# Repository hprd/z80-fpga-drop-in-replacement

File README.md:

# z80-fpga-drop-in-replacement
UT Austin Fall 2025-Spring 2026 Senior Design Project for developing a Zilog Z80 CPU drop-in replacement using an FPGA.

Relevant links and information from previous group's iteration:
- [Instruction Set](https://map.grauw.nl/resources/z80instr.php)
- [Z80 User Manual](https://www.zilog.com/docs/z80/um0080.pdf)
- [Master Reference Website](http://z80.info/)
- [Timing Quirks](https://floooh.github.io/2021/12/06/z80-instruction-timing.html#extra-clock-cycles)

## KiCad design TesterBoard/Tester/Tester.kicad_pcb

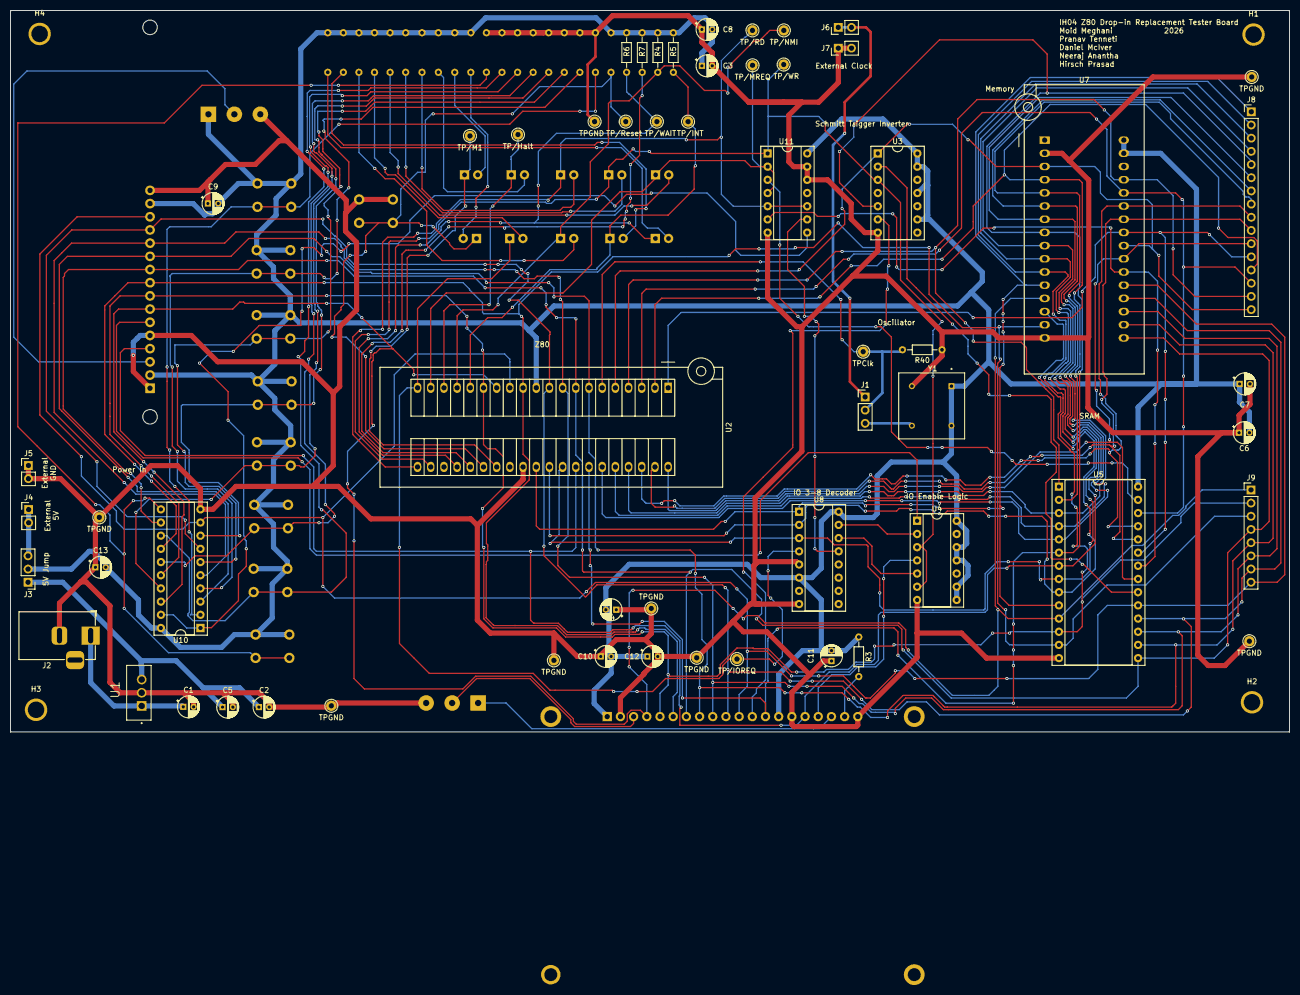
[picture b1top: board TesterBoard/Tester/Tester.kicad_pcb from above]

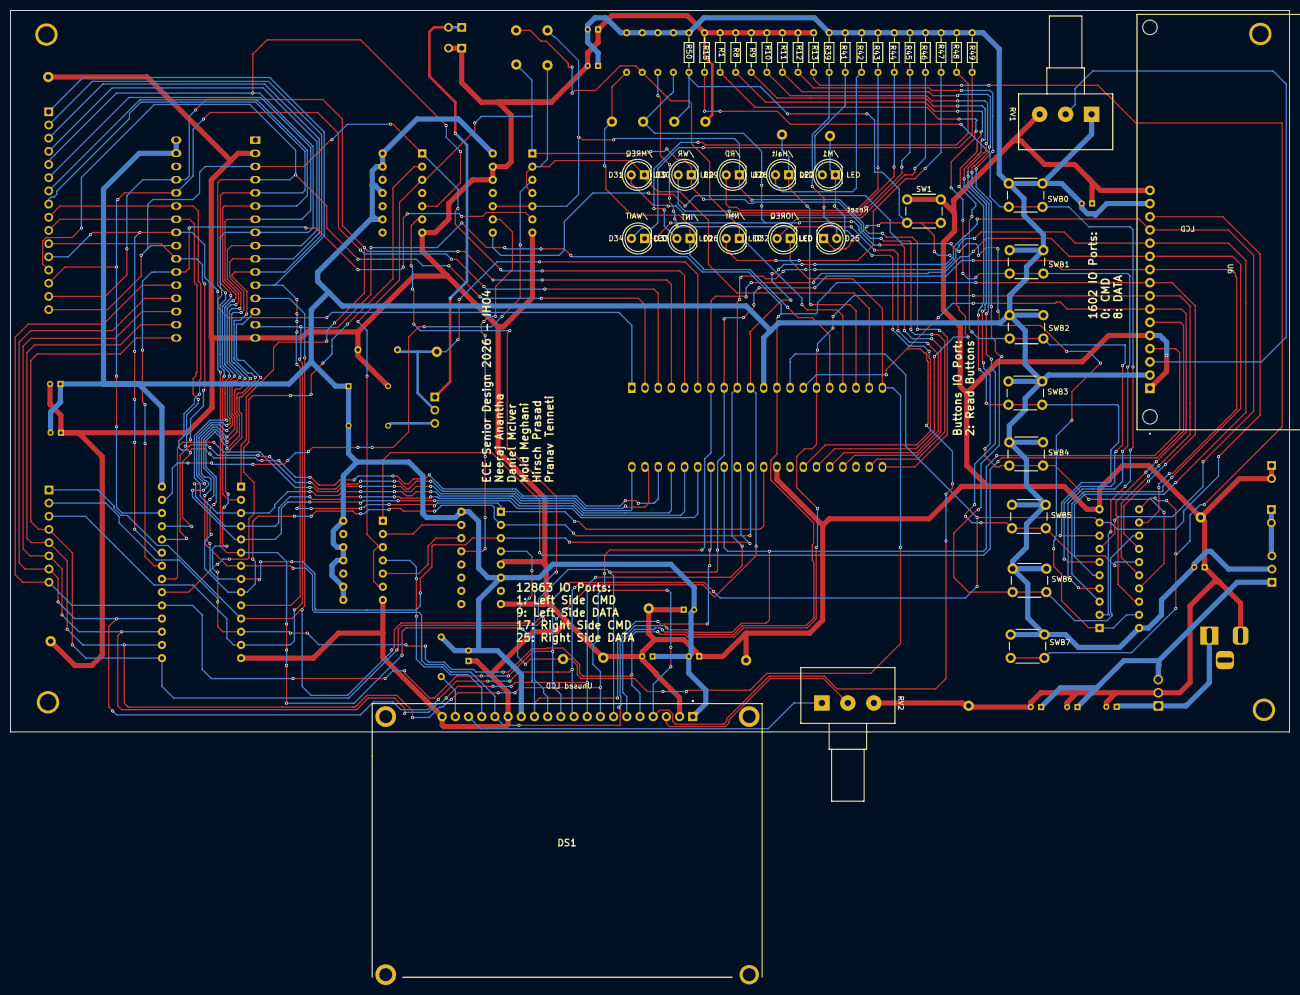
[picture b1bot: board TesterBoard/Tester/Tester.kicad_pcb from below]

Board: 2 copper layers, 246.3 x 138.9 mm, 103 parts (42 on the bottom side), 75 nets.

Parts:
C1: 330nF; CP_Radial_D4.0mm_P2.00mm
C2, C3, C4, C6, C7, C8, C9, C10, C11, C12, C13: 100nF; CP_Radial_D4.0mm_P2.00mm
C5: 10uF; CP_Radial_D4.0mm_P2.00mm
D25, D26, D27, D28, D29, D30, D31, D32, D33, D34: LED; LED_D5.0mm
DS1: NHD-12864WG-BTMI-V#N; NHD12864WGBTMIVN
H1, H2, H3, H4: MountingHole_4_40
J1, J3: Conn_01x03_Pin; PinHeader_1x03_P2.54mm_Vertical
J2: PJ-102A; BarrelJack_Horizontal
J4, J5, J6, J7: Conn_01x02_Pin; PinHeader_1x02_P2.54mm_Vertical
J8: Conn_01x16_Pin; PinHeader_1x16_P2.54mm_Vertical
J9: Conn_01x08_Pin; PinHeader_1x08_P2.54mm_Vertical
R1, R8, R9, R10, R11, R12, R13, R15: 1k; R_Axial_DIN0204_L3.6mm_D1.6mm_P7.62mm_Horizontal
R3, R39, R40, R41, R42, R43, R44, R45, R46, R47, R48, R49, R50: 1K; R_Axial_DIN0204_L3.6mm_D1.6mm_P7.62mm_Horizontal
R4, R5, R6, R7: 10K; R_Axial_DIN0204_L3.6mm_D1.6mm_P7.62mm_Horizontal
RV1, RV2: R_Potentiometer; Potentiometer_Alps_RK163_Single_Horizontal
SW1: SW_Push; SW_PUSH_6mm
SWB0, SWB1, SWB2, SWB3, SWB4, SWB5, SWB6, SWB7: SW_Push; SW_PUSH_6mm
TP/Halt: TestPoint; Pin_D1.0mm_L10.0mm
TP/INT: TestPoint; Pin_D1.0mm_L10.0mm
TP/IOREQ: TestPoint; Pin_D1.0mm_L10.0mm
TP/M1: TestPoint; Pin_D1.0mm_L10.0mm
TP/MREQ: TestPoint; Pin_D1.0mm_L10.0mm
TP/NMI: TestPoint; Pin_D1.0mm_L10.0mm
TP/RD: TestPoint; Pin_D1.0mm_L10.0mm
TP/Reset: TestPoint; Pin_D1.0mm_L10.0mm
TP/WAIT: TestPoint; Pin_D1.0mm_L10.0mm
TP/WR: TestPoint; Pin_D1.0mm_L10.0mm
TPClk: TestPoint; Pin_D1.0mm_L10.0mm
TPGND: TestPoint; Pin_D1.0mm_L10.0mm
TPGND#2, TPGND#3, TPGND#4, TPGND#5, TPGND#6, TPGND#7, TPGND#8: TestPoint; Pin_D1.0mm_L10.0mm
U1: L7805; TO254P1054X470X2600-3
U2: Z80CPU; 3M_Textool_240-1288-00-0602J_2x20_P2.54mm
U3: 74LS14; DIP-14_W7.62mm_Socket
U4: 74LS02; DIP-14_W7.62mm_Socket
U5: CY62256-70PC; DIP-28_W15.24mm_Socket
U6: LCD-16X2; MODULE_LCD-16X2
U7: SST39SF010; DIP_Socket-32_W11.9_W12.7_W15.24_W17.78_W18.5_3M_232-1285-0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
U8: 74HC138; DIP-16_W7.62mm_Socket
U10: 74HC244; DIP-20_W7.62mm_Socket
U11: 74LS32; DIP-14_W7.62mm_Socket
Y1: ACH-4.000MHZ-EK; XTAL_ACH-4.000MHZ-EK

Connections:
1602_Enable: U4.1, U6.6 (E)
12864_Enable: DS1.17 (E), U4.4
12864_VEE: DS1.18 (VEE), RV2.1
+5V: C3.1, C4.2, C6.2, C7.1, C8.2, C9.2, C10.2, C11.2, C12.1, C13.2, DS1.1 (VDD), DS1.14 (~RST), J3.2, R3.1, R4.1, R5.2, R6.1, R7.1, R39.1, R41.1, R42.1, R43.1, R44.1, R45.1, R46.1, R47.1, R48.1, R49.1, R50.1, RV1.1, SWB0.1, SWB1.1, SWB2.1, SWB3.1, SWB4.1, SWB5.1, SWB6.1, SWB7.1, U2.11 (VCC), U3.9, U3.11, U3.13, U3.14 (VCC), U4.8, U4.9, U4.11, U4.12, U4.14 (VCC), U5.28 (VCC), U6.2 (VDD), U6.15 (A), U7.31 (PGM), U7.32 (VCC), U8.6 (E2), U8.16 (VCC), U10.20 (VCC), U11.14 (VCC), Y1.1 (TRI-STATE/NC), Y1.8 (VDD)
+9V: C1.1, J2.1, U1.1 (IN)
Address0: J8.1, U2.30 (A0), U5.10 (A0), U7.12 (A0), U8.1 (A0)
Address1: J8.2, U2.31 (A1), U5.9 (A1), U7.11 (A1), U8.2 (A1)
Address2: J8.3, U2.32 (A2), U5.8 (A2), U7.10 (A2), U8.3 (A2)
Address3: DS1.16 (D/~I), J8.4, U2.33 (A3), U5.7 (A3), U6.4 (RS), U7.9 (A3)
Address4: DS1.13 (CS2), J8.5, U2.34 (A4), U3.5, U5.6 (A4), U7.8 (A4)
Address5: J8.6, U2.35 (A5), U5.5 (A5), U7.7 (A5)
Address6: J8.7, U2.36 (A6), U5.4 (A6), U7.6 (A6)
Address7: J8.8, U2.37 (A7), U5.3 (A7), U7.5 (A7)
Address8: J8.9, U2.38 (A8), U5.25 (A8), U7.27 (A8)
Address9: J8.10, U2.39 (A9), U5.24 (A9), U7.26 (A9)
Address10: J8.11, U2.40 (A10), U5.21 (A10), U7.23 (A10)
Address11: J8.12, U2.1 (A11), U5.23 (A11), U7.25 (A11)
Address12: J8.13, U2.2 (A12), U5.2 (A12), U7.4 (A12)
Address13: J8.14, U2.3 (A13), U5.26 (A13), U7.28 (A13)
Address14: J8.15, U2.4 (A14), U5.1 (A14), U7.29 (A14)
Address15: J8.16, U2.5 (A15), U3.1, U7.3 (A15), U7.24 (OE)
B0: R15.2, SWB0.2, U10.2 (1A0)
B1: R1.2, SWB1.2, U10.4 (1A1)
B2: R8.2, SWB2.2, U10.6 (1A2)
B3: R9.2, SWB3.2, U10.8 (1A3)
B4: R10.2, SWB4.2, U10.17 (2A0)
B5: R11.2, SWB5.2, U10.15 (2A1)
B6: R12.2, SWB6.2, U10.13 (2A2)
B7: R13.2, SWB7.2, U10.11 (2A3)
Barrel_5V: C2.1, C5.1, J3.1, U1.3 (OUT)
Clk: J1.2, R40.2, TPClk.1, U2.6 (~CLK)
Data0: DS1.4 (DB0), J9.1, U2.14 (D0), U5.11 (Q0), U6.7 (DB0), U7.13 (D0), U10.18 (1Y0)
Data1: DS1.5 (DB1), J9.2, U2.15 (D1), U5.12 (Q1), U6.8 (DB1), U7.14 (D1), U10.16 (1Y1)
Data2: DS1.6 (DB2), J9.3, U2.12 (D2), U5.13 (Q2), U6.9 (DB2), U7.15 (D2), U10.14 (1Y2)
Data3: DS1.7 (DB3), J9.4, U2.8 (D3), U5.15 (Q3), U6.10 (DB3), U7.17 (D3), U10.12 (1Y3)
Data4: DS1.8 (DB4), J9.5, U2.7 (D4), U5.16 (Q4), U6.11 (DB4), U7.18 (D4), U10.3 (2Y0)
Data5: DS1.9 (DB5), J9.6, U2.9 (D5), U5.17 (Q5), U6.12 (DB5), U7.19 (D5), U10.5 (2Y1)
Data6: DS1.10 (DB6), J9.7, U2.10 (D6), U5.18 (Q6), U6.13 (DB6), U7.20 (D6), U10.7 (2Y2)
Data7: DS1.11 (DB7), J9.8, U2.13 (D7), U5.19 (Q7), U6.14 (DB7), U7.21 (D7), U10.9 (2Y3)
EXTERNAL_CLOCK: J1.1, J6.1, J6.2
Ext_5V: J3.3, J4.1, J4.2
GND: C1.2, C2.2, C3.2, C4.1, C5.2, C6.1, C7.2, C8.1, C9.1, C10.1, C11.1, C12.2, C13.1, DS1.2 (VSS), DS1.15 (R/~W), DS1.20 (K), J2.2, J5.1, J5.2, J7.1, J7.2, R1.1, R8.1, R9.1, R10.1, R11.1, R12.1, R13.1, R15.1, R40.1, RV1.3, RV2.3, SW1.1, TPGND.1, TPGND#2.1, TPGND#3.1, TPGND#4.1, TPGND#5.1, TPGND#6.1, TPGND#7.1, TPGND#8.1, U1.2 (GND), U2.29 (GND), U3.7 (GND), U4.7 (GND), U5.14 (GND), U6.1 (VSS), U6.5 (R/W), U6.16 (K), U7.2 (A16), U7.16 (GND), U8.5 (~E1), U8.8 (GND), U10.10 (GND), U11.7 (GND), U11.12, U11.13, Y1.4 (CASE_GND)
unnamed: D25.2 (A), R39.2
unnamed: D26.2 (A), R47.2
unnamed: D27.2 (A), R41.2
unnamed: D28.2 (A), R42.2
unnamed: D29.2 (A), R43.2
unnamed: D30.2 (A), R44.2
unnamed: D31.2 (A), R45.2
unnamed: D32.2 (A), R46.2
unnamed: D33.2 (A), R48.2
unnamed: D34.2 (A), R49.2
unnamed: DS1.19 (A), R3.2
unnamed: DS1.3 (V0), RV2.2
unnamed: R7.2, U2.25 (~BUSRQ)
unnamed: U3.2, U5.20 (~CS)
unnamed: U5.22 (~OE), U7.22 (CE), U11.6
unnamed: U5.27 (~WE), U11.3
unnamed: RV1.2, U6.3 (VO)
OSC_CLOCK: J1.3, Y1.5 (OUTPUT)
/1602_Select: U4.2, U8.15 (~Y0)
/12864_Select: U4.5, U8.14 (~Y1)
/Address4: DS1.12 (CS1), U3.6
/Buttons_Enable: U10.1 (1OE), U10.19 (2OE), U11.8
/Buttons_Select: U8.13 (~Y2), U11.9
/Halt: D28.1 (K), TP/Halt.1, U2.18 (~HALT)
/INT: D33.1 (K), R5.1, TP/INT.1, U2.16 (~INT)
/IOREQ: D32.1 (K), TP/IOREQ.1, U2.20 (~IORQ), U8.4 (~E0)
/M1: D27.1 (K), TP/M1.1, U2.27 (~M1)
/MREQ: D31.1 (K), TP/MREQ.1, U2.19 (~MREQ), U11.2, U11.4
/NMI: D26.1 (K), R4.2, TP/NMI.1, U2.17 (~NMI)
/RD: D29.1 (K), TP/RD.1, U2.21 (~RD), U11.5, U11.10
/Reset: D25.1 (K), R50.2, SW1.2, TP/Reset.1, U2.26 (~RESET)
/WAIT: D34.1 (K), R6.2, TP/WAIT.1, U2.24 (~WAIT)
/WR: D30.1 (K), TP/WR.1, U2.22 (~WR), U3.3, U4.3, U4.6, U11.1

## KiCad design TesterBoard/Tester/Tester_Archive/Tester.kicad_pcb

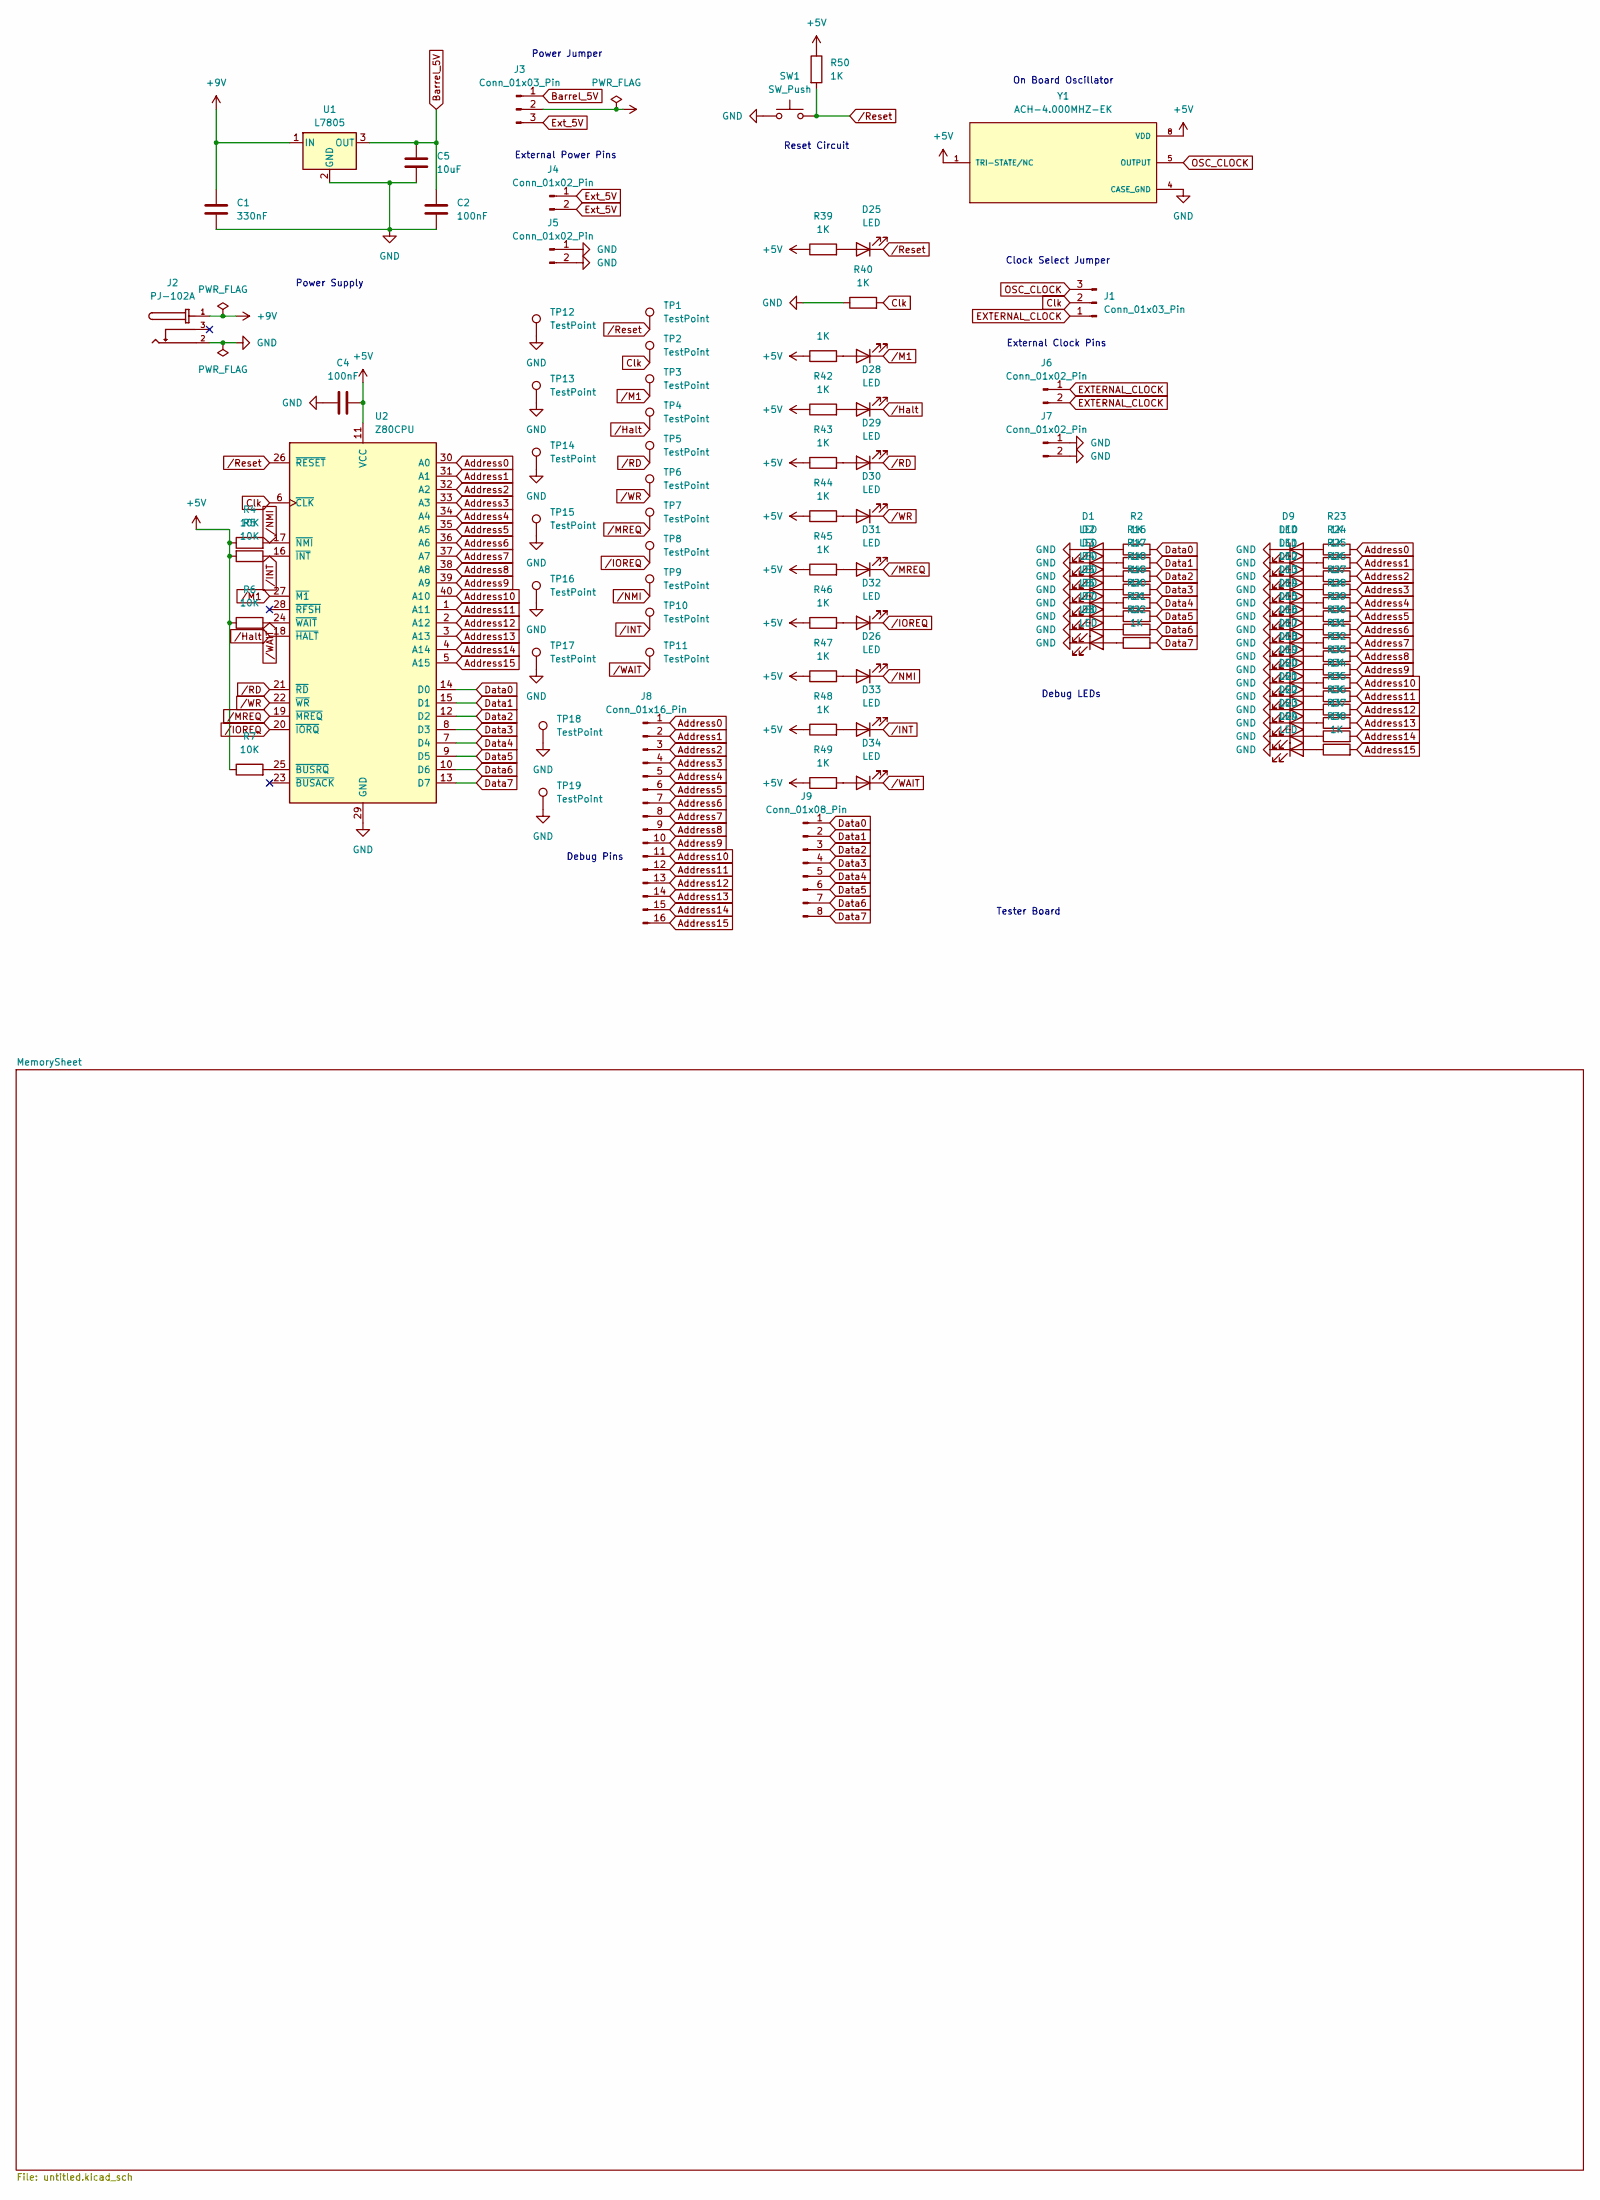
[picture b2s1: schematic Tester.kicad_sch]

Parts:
C1: 330nF; CP_Radial_D4.0mm_P2.00mm
C2, C4: 100nF; CP_Radial_D4.0mm_P2.00mm
C5: 10uF; CP_Radial_D4.0mm_P2.00mm
D1, D2, D3, D4, D5, D6, D7, D8, D9, D10, D11, D12, D13, D14, D15, D16, D17, D18, D19, D20, D21, D22, D23, D24, D25, D26, D27, D28, D29, D30, D31, D32, D33, D34: LED; LED_D5.0mm
J1, J3: Conn_01x03_Pin; PinHeader_1x03_P2.54mm_Vertical
J2: PJ-102A; CUI_PJ-102A
J4, J5, J6, J7: Conn_01x02_Pin; PinHeader_1x02_P2.54mm_Vertical
J8: Conn_01x16_Pin; PinHeader_1x16_P2.54mm_Vertical
J9: Conn_01x08_Pin; PinHeader_1x08_P2.54mm_Vertical
R2, R16, R17, R18, R19, R20, R21, R22, R23, R24, R25, R26, R27, R28, R29, R30, R31, R32, R33, R34, R35, R36, R37, R38, R39, R40, R41, R42, R43, R44, R45, R46, R47, R48, R49, R50: 1K; R_Axial_DIN0204_L3.6mm_D1.6mm_P7.62mm_Horizontal
R4, R5, R6, R7: 10K; R_Axial_DIN0204_L3.6mm_D1.6mm_P7.62mm_Horizontal
SW1: SW_Push; SW_PUSH_6mm
TP1, TP2, TP3, TP4, TP5, TP6, TP7, TP8, TP9, TP10, TP11, TP12, TP13, TP14, TP15, TP16, TP17, TP18, TP19: TestPoint; Pin_D1.0mm_L10.0mm
U1: L7805; TO254P1054X470X2600-3
U2: Z80CPU; 3M_Textool_240-1288-00-0602J_2x20_P2.54mm
Y1: ACH-4.000MHZ-EK; XTAL_ACH-4.000MHZ-EK; PARTREV 11.15.2016

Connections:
+5V: C4.2, J3.2, R4.1, R5.2, R6.1, R7.1, R39.1, R41.1, R42.1, R43.1, R44.1, R45.1, R46.1, R47.1, R48.1, R49.1, R50.1, U2.11 (VCC), Y1.1 (TRI-STATE/NC), Y1.8 (VDD); also elsewhere on the board
+9V: C1.1, J2.1, U1.1 (IN)
Address0: J8.1, R23.2, U2.30 (A0); also elsewhere on the board
Address1: J8.2, R24.2, U2.31 (A1); also elsewhere on the board
Address2: J8.3, R25.2, U2.32 (A2); also elsewhere on the board
Address3: J8.4, R26.2, U2.33 (A3); also elsewhere on the board
Address4: J8.5, R27.2, U2.34 (A4); also elsewhere on the board
Address5: J8.6, R28.2, U2.35 (A5); also elsewhere on the board
Address6: J8.7, R29.2, U2.36 (A6); also elsewhere on the board
Address7: J8.8, R30.2, U2.37 (A7); also elsewhere on the board
Address8: J8.9, R31.2, U2.38 (A8); also elsewhere on the board
Address9: J8.10, R32.2, U2.39 (A9); also elsewhere on the board
Address10: J8.11, R33.2, U2.40 (A10); also elsewhere on the board
Address11: J8.12, R34.2, U2.1 (A11); also elsewhere on the board
Address12: J8.13, R35.2, U2.2 (A12); also elsewhere on the board
Address13: J8.14, R36.2, U2.3 (A13); also elsewhere on the board
Address14: J8.15, R37.2, U2.4 (A14); also elsewhere on the board
Address15: J8.16, R38.2, U2.5 (A15); also elsewhere on the board
Barrel_5V: C2.1, C5.1, J3.1, U1.3 (OUT)
Clk: J1.2, R40.2, TP2.1, U2.6 (~CLK)
Data0: J9.1, R2.2, U2.14 (D0); also elsewhere on the board
Data1: J9.2, R16.2, U2.15 (D1); also elsewhere on the board
Data2: J9.3, R17.2, U2.12 (D2); also elsewhere on the board
Data3: J9.4, R18.2, U2.8 (D3); also elsewhere on the board
Data4: J9.5, R19.2, U2.7 (D4); also elsewhere on the board
Data5: J9.6, R20.2, U2.9 (D5); also elsewhere on the board
Data6: J9.7, R21.2, U2.10 (D6); also elsewhere on the board
Data7: J9.8, R22.2, U2.13 (D7); also elsewhere on the board
EXTERNAL_CLOCK: J1.1, J6.1, J6.2
Ext_5V: J3.3, J4.1, J4.2
GND: C1.2, C2.2, C4.1, C5.2, D1.1 (K), D2.1 (K), D3.1 (K), D4.1 (K), D5.1 (K), D6.1 (K), D7.1 (K), D8.1 (K), D9.1 (K), D10.1 (K), D11.1 (K), D12.1 (K), D13.1 (K), D14.1 (K), D15.1 (K), D16.1 (K), D17.1 (K), D18.1 (K), D19.1 (K), D20.1 (K), D21.1 (K), D22.1 (K), D23.1 (K), D24.1 (K), J2.2, J5.1, J5.2, J7.1, J7.2, R40.1, SW1.1, TP12.1, TP13.1, TP14.1, TP15.1, TP16.1, TP17.1, TP18.1, TP19.1, U1.2 (GND), U2.29 (GND), Y1.4 (CASE_GND); also elsewhere on the board
unnamed: D1.2 (A), R2.1
unnamed: D2.2 (A), R16.1
unnamed: D3.2 (A), R17.1
unnamed: D4.2 (A), R18.1
unnamed: D5.2 (A), R19.1
unnamed: D6.2 (A), R20.1
unnamed: D7.2 (A), R21.1
unnamed: D8.2 (A), R22.1
unnamed: D9.2 (A), R23.1
unnamed: D10.2 (A), R24.1
unnamed: D11.2 (A), R25.1
unnamed: D12.2 (A), R26.1
unnamed: D13.2 (A), R27.1
unnamed: D14.2 (A), R28.1
unnamed: D15.2 (A), R29.1
unnamed: D16.2 (A), R30.1
unnamed: D17.2 (A), R31.1
unnamed: D18.2 (A), R32.1
unnamed: D19.2 (A), R33.1
unnamed: D20.2 (A), R34.1
unnamed: D21.2 (A), R35.1
unnamed: D22.2 (A), R36.1
unnamed: D23.2 (A), R37.1
unnamed: D24.2 (A), R38.1
unnamed: D25.2 (A), R39.2
unnamed: D26.2 (A), R47.2
unnamed: D27.2 (A), R41.2
unnamed: D28.2 (A), R42.2
unnamed: D29.2 (A), R43.2
unnamed: D30.2 (A), R44.2
unnamed: D31.2 (A), R45.2
unnamed: D32.2 (A), R46.2
unnamed: D33.2 (A), R48.2
unnamed: D34.2 (A), R49.2
unnamed: R7.2, U2.25 (~BUSRQ)
OSC_CLOCK: J1.3, Y1.5 (OUTPUT)
/Halt: D28.1 (K), TP4.1, U2.18 (~HALT)
/INT: D33.1 (K), R5.1, TP10.1, U2.16 (~INT)
/IOREQ: D32.1 (K), TP8.1, U2.20 (~IORQ); also elsewhere on the board
/M1: D27.1 (K), TP3.1, U2.27 (~M1)
/MREQ: D31.1 (K), TP7.1, U2.19 (~MREQ); also elsewhere on the board
/NMI: D26.1 (K), R4.2, TP9.1, U2.17 (~NMI)
/RD: D29.1 (K), TP5.1, U2.21 (~RD); also elsewhere on the board
/Reset: D25.1 (K), R50.2, SW1.2, TP1.1, U2.26 (~RESET)
/WAIT: D34.1 (K), R6.2, TP11.1, U2.24 (~WAIT)
/WR: D30.1 (K), TP6.1, U2.22 (~WR); also elsewhere on the board

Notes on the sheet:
Tester Board
Debug LEDs
Reset Circuit
Clock Select Jumper
Debug Pins
External Clock Pins
Power Jumper
External Power Pins
On Board Oscillator
Power Supply

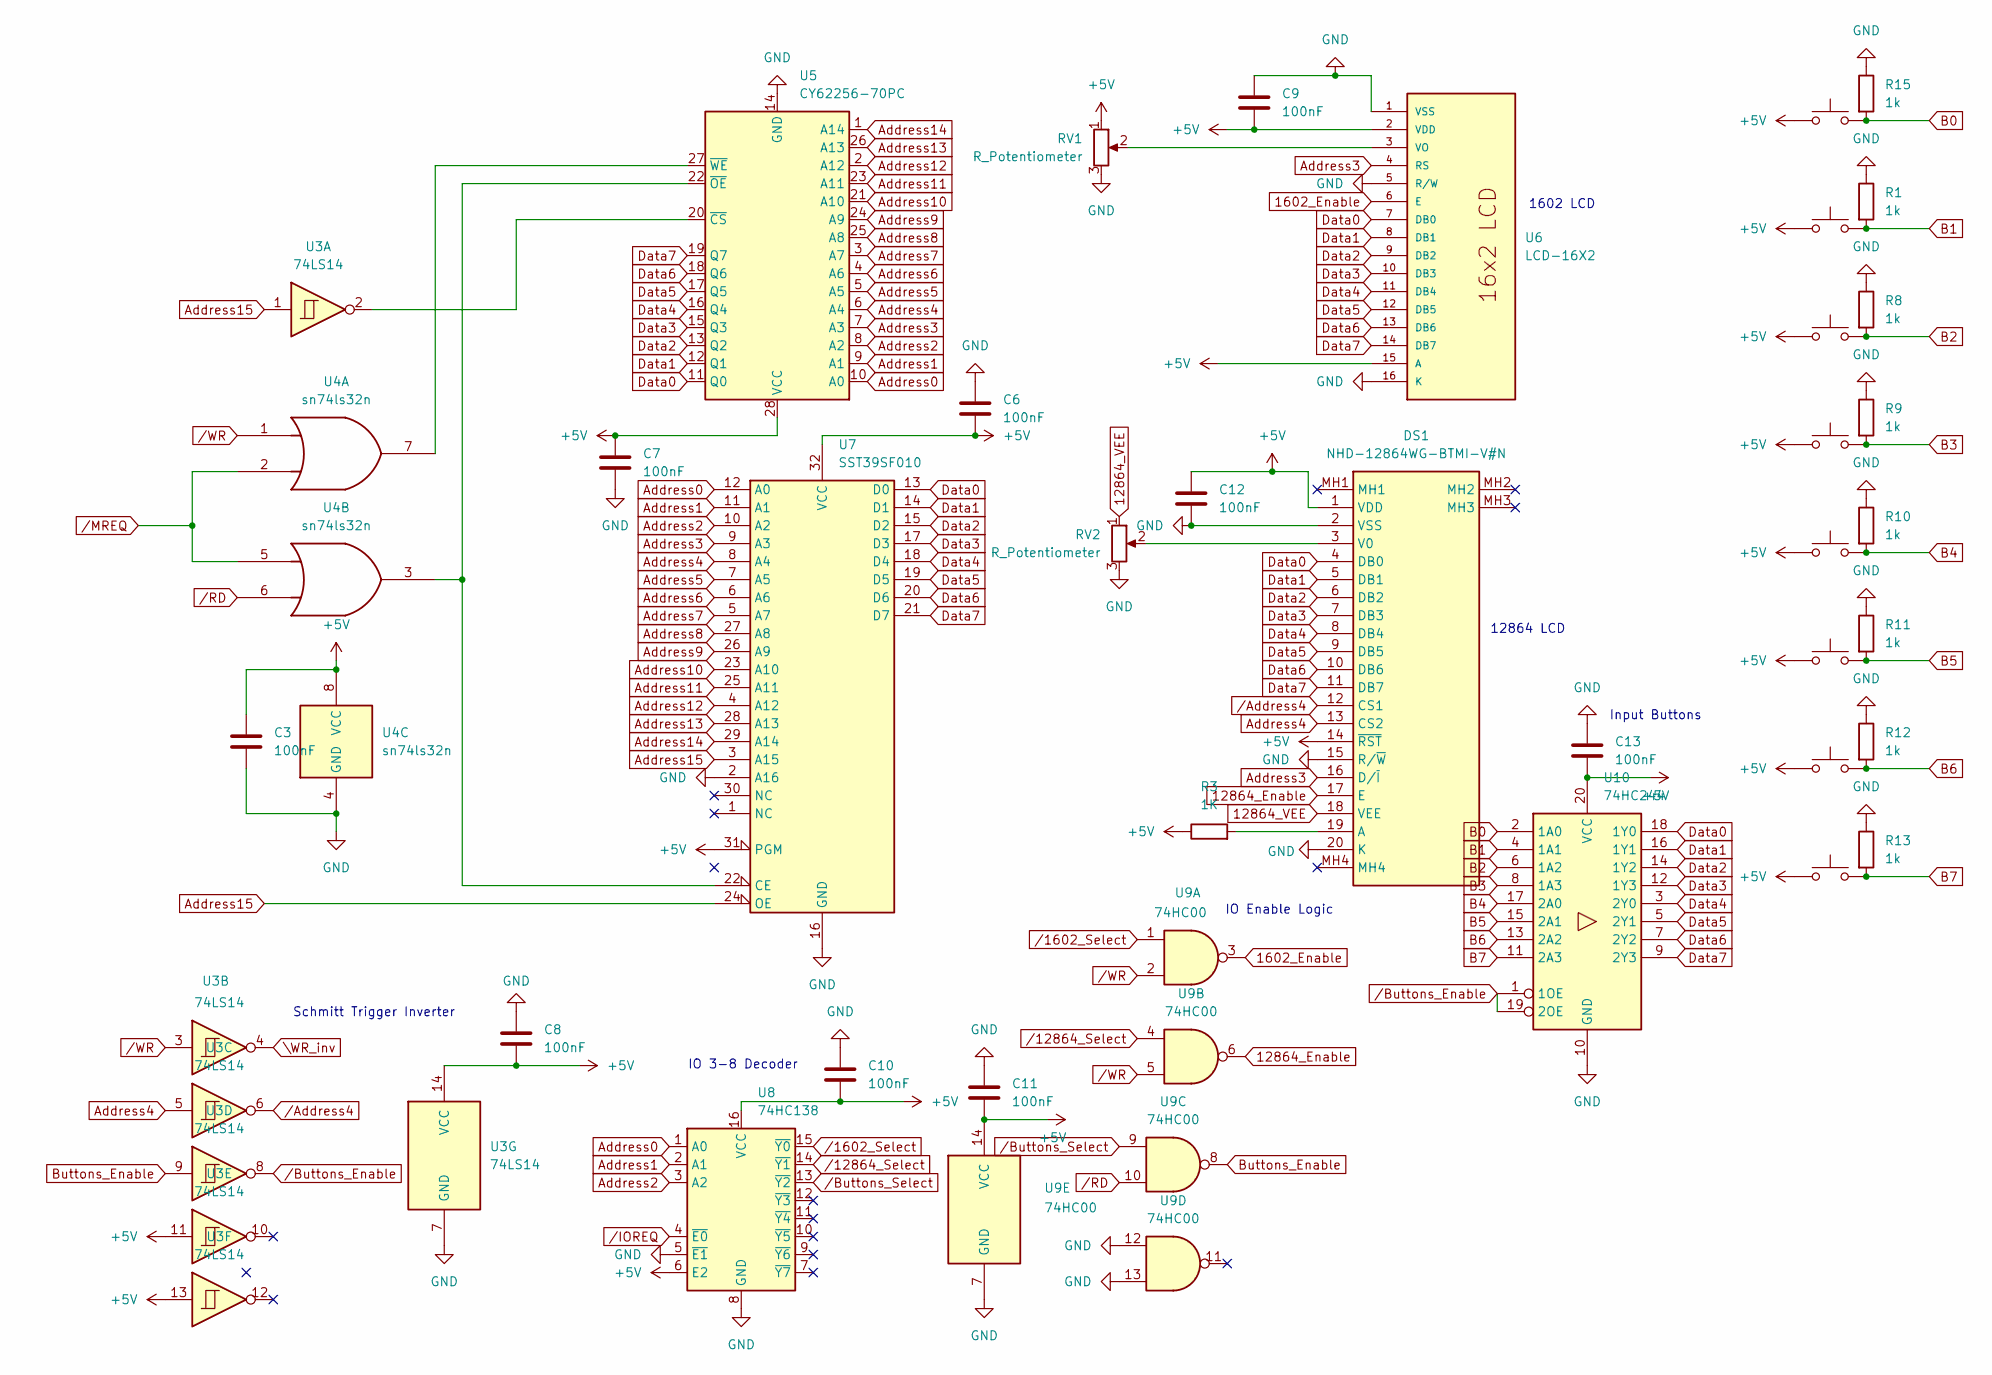
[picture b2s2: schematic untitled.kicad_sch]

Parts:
C3, C6, C7, C8, C9, C10, C11, C12, C13: 100nF; CP_Radial_D4.0mm_P2.00mm
DS1: NHD-12864WG-BTMI-V#N; NHD12864WGBTMIVN; Manufacturer_Part_Number NHD-12864WG-BTMI-V#N; Mouser Part Number 763-12864WG-BTMI-VN
R1, R8, R9, R10, R11, R12, R13, R15: 1k; R_Axial_DIN0204_L3.6mm_D1.6mm_P7.62mm_Horizontal
R3: 1K; R_Axial_DIN0204_L3.6mm_D1.6mm_P7.62mm_Horizontal
RV1, RV2: R_Potentiometer; Potentiometer_Alps_RK163_Single_Horizontal
SW2, SW3, SW4, SW5, SW6, SW7, SW8, SW10: SW_Push; SW_PUSH_6mm
U3: 74LS14; DIP-14_W7.62mm_Socket
U4: sn74ls32n; DIP-14_W7.62mm_Socket
U5: CY62256-70PC; DIP-28_W15.24mm
U6: LCD-16X2; MODULE_LCD-16X2; PARTREV N/A
U7: SST39SF010; DIP_Socket-32_W11.9_W12.7_W15.24_W17.78_W18.5_3M_232-1285-0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
U8: 74HC138; DIP-16_W7.62mm_Socket
U9: 74HC00; DIP-14_W7.62mm_Socket
U10: 74HC244; DIP-20_W7.62mm_Socket

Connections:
1602_Enable: U6.6 (E), U9.3
12864_Enable: DS1.17 (E), U9.6
12864_VEE: DS1.18 (VEE), RV2.1
+5V: C3.1, C6.2, C7.1, C8.2, C9.2, C10.2, C11.2, C12.1, C13.2, DS1.1 (VDD), DS1.14 (~RST), R3.1, RV1.1, SW2.1, SW3.1, SW4.1, SW5.1, SW6.1, SW7.1, SW8.1, SW10.1, U3.11, U3.13, U3.14 (VCC), U4.8 (VCC), U5.28 (VCC), U6.2 (VDD), U6.15 (A), U7.31 (PGM), U7.32 (VCC), U8.6 (E2), U8.16 (VCC), U9.14 (VCC), U10.20 (VCC); also elsewhere on the board
Address0: U5.10 (A0), U7.12 (A0), U8.1 (A0); also elsewhere on the board
Address1: U5.9 (A1), U7.11 (A1), U8.2 (A1); also elsewhere on the board
Address2: U5.8 (A2), U7.10 (A2), U8.3 (A2); also elsewhere on the board
Address3: DS1.16 (D/~I), U5.7 (A3), U6.4 (RS), U7.9 (A3); also elsewhere on the board
Address4: DS1.13 (CS2), U3.5, U5.6 (A4), U7.8 (A4); also elsewhere on the board
Address5: U5.5 (A5), U7.7 (A5); also elsewhere on the board
Address6: U5.4 (A6), U7.6 (A6); also elsewhere on the board
Address7: U5.3 (A7), U7.5 (A7); also elsewhere on the board
Address8: U5.25 (A8), U7.27 (A8); also elsewhere on the board
Address9: U5.24 (A9), U7.26 (A9); also elsewhere on the board
Address10: U5.21 (A10), U7.23 (A10); also elsewhere on the board
Address11: U5.23 (A11), U7.25 (A11); also elsewhere on the board
Address12: U5.2 (A12), U7.4 (A12); also elsewhere on the board
Address13: U5.26 (A13), U7.28 (A13); also elsewhere on the board
Address14: U5.1 (A14), U7.29 (A14); also elsewhere on the board
Address15: U3.1, U7.3 (A15), U7.24 (OE); also elsewhere on the board
B0: R15.2, SW10.2, U10.2 (1A0)
B1: R1.2, SW2.2, U10.4 (1A1)
B2: R8.2, SW3.2, U10.6 (1A2)
B3: R9.2, SW4.2, U10.8 (1A3)
B4: R10.2, SW5.2, U10.17 (2A0)
B5: R11.2, SW6.2, U10.15 (2A1)
B6: R12.2, SW7.2, U10.13 (2A2)
B7: R13.2, SW8.2, U10.11 (2A3)
Buttons_Enable: U3.9, U9.8
Data0: DS1.4 (DB0), U5.11 (Q0), U6.7 (DB0), U7.13 (D0), U10.18 (1Y0); also elsewhere on the board
Data1: DS1.5 (DB1), U5.12 (Q1), U6.8 (DB1), U7.14 (D1), U10.16 (1Y1); also elsewhere on the board
Data2: DS1.6 (DB2), U5.13 (Q2), U6.9 (DB2), U7.15 (D2), U10.14 (1Y2); also elsewhere on the board
Data3: DS1.7 (DB3), U5.15 (Q3), U6.10 (DB3), U7.17 (D3), U10.12 (1Y3); also elsewhere on the board
Data4: DS1.8 (DB4), U5.16 (Q4), U6.11 (DB4), U7.18 (D4), U10.3 (2Y0); also elsewhere on the board
Data5: DS1.9 (DB5), U5.17 (Q5), U6.12 (DB5), U7.19 (D5), U10.5 (2Y1); also elsewhere on the board
Data6: DS1.10 (DB6), U5.18 (Q6), U6.13 (DB6), U7.20 (D6), U10.7 (2Y2); also elsewhere on the board
Data7: DS1.11 (DB7), U5.19 (Q7), U6.14 (DB7), U7.21 (D7), U10.9 (2Y3); also elsewhere on the board
GND: C3.2, C6.1, C7.2, C8.1, C9.1, C10.1, C11.1, C12.2, C13.1, DS1.2 (VSS), DS1.15 (R/~W), DS1.20 (K), R1.1, R8.1, R9.1, R10.1, R11.1, R12.1, R13.1, R15.1, RV1.3, RV2.3, U3.7 (GND), U4.4 (GND), U5.14 (GND), U6.1 (VSS), U6.5 (R/W), U6.16 (K), U7.2 (A16), U7.16 (GND), U8.5 (~E1), U8.8 (GND), U9.7 (GND), U9.12, U9.13, U10.10 (GND); also elsewhere on the board
unnamed: DS1.19 (A), R3.2
unnamed: DS1.3 (V0), RV2.2
unnamed: U3.2, U5.20 (~CS)
unnamed: U4.3, U5.22 (~OE), U7.22 (CE)
unnamed: U4.7, U5.27 (~WE)
unnamed: RV1.2, U6.3 (VO)
\WR_inv: U3.4
/1602_Select: U8.15 (~Y0), U9.1
/12864_Select: U8.14 (~Y1), U9.4
/Address4: DS1.12 (CS1), U3.6
/Buttons_Enable: U3.8, U10.1 (1OE), U10.19 (2OE)
/Buttons_Select: U8.13 (~Y2), U9.9
/IOREQ: U8.4 (~E0); also elsewhere on the board
/MREQ: U4.2, U4.5; also elsewhere on the board
/RD: U4.6, U9.10; also elsewhere on the board
/WR: U3.3, U4.1, U9.2, U9.5; also elsewhere on the board

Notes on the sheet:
Schmitt Trigger Inverter
12864 LCD
1602 LCD
IO Enable Logic
IO 3-8 Decoder
Input Buttons

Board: 2 copper layers, 147 parts (0 on the bottom side), 100 nets, no tracks yet.
